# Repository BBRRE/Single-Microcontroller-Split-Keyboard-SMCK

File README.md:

# Single-Microcontroller-Split-Keyboard-SMCK
Design for a split keyboard that only uses a singular microcontroller, passive side uses a cascade of shift registors to send data through a singular serial wire leaving the 2 sides connected by only 5 wires (GND, VCC, CLK, PL, DATA)

## Schematics

## Front of the PCB

## Back of the PCB

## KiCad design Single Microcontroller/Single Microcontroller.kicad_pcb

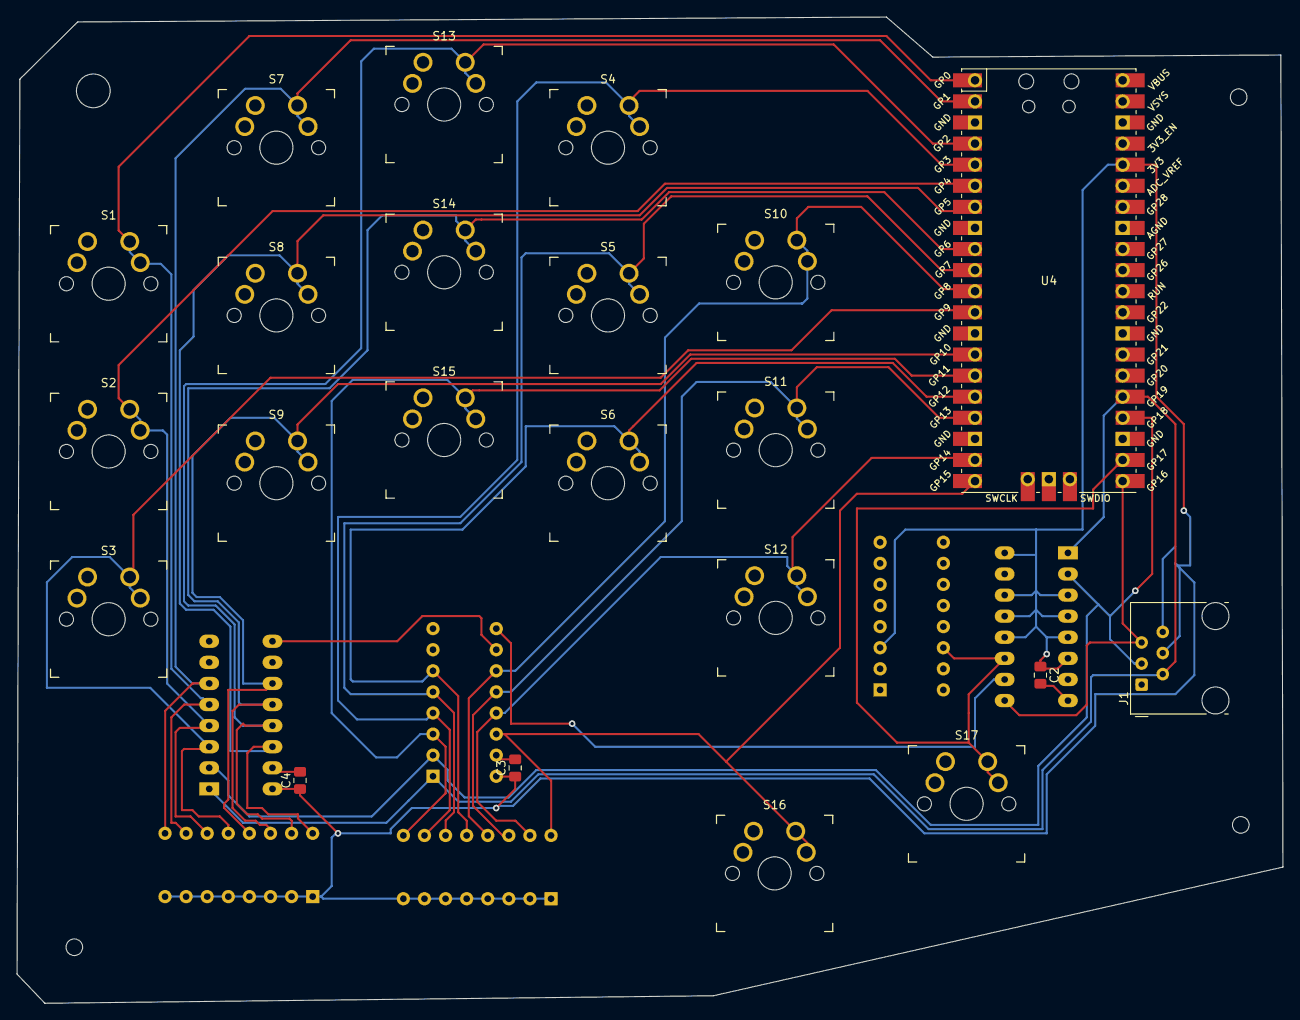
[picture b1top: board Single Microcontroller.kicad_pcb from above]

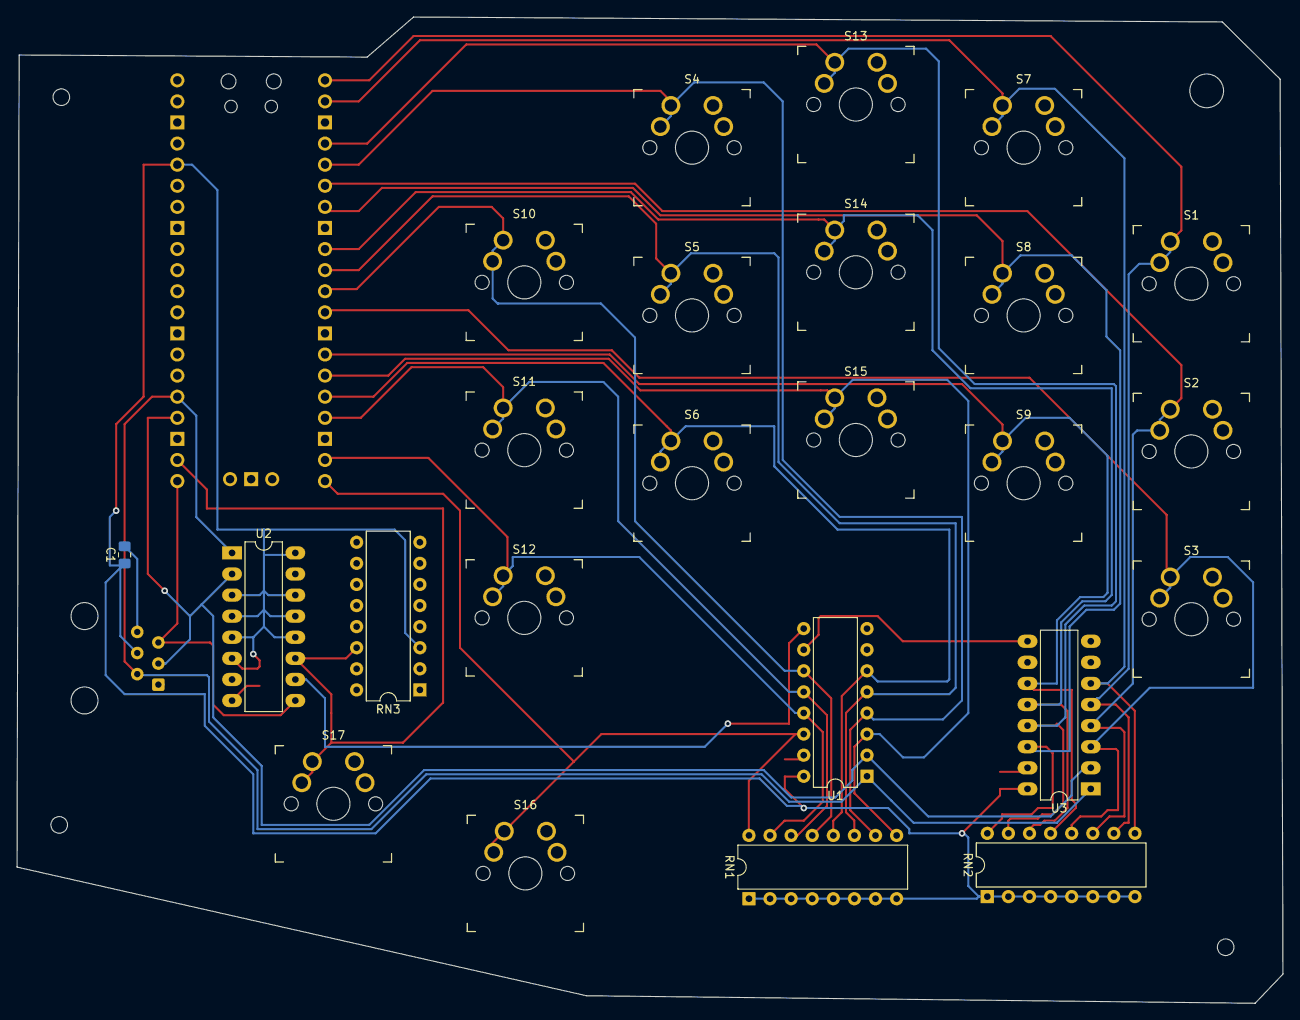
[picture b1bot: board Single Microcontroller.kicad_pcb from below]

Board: 2 copper layers, 152.4 x 118.8 mm, 29 parts (7 on the bottom side), 24 nets.

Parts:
C1, C2, C3, C4: C; C_0805_2012Metric_Pad1.18x1.45mm_HandSolder
J1: RJ12; RJ12_Amphenol_54601-x06_Horizontal
RN1, RN2, RN3: R_Pack08; DIP-16_W7.62mm
S1, S2, S3, S4, S5, S6, S7, S8, S9, S10, S11, S12, S13, S14, S15, S16, S17: Keyswitch; SW_MX_reversible
U1: 74HC165; DIP-16_W7.62mm
U2, U3: 74HC165; DIP-16_W7.62mm_LongPads
U4: Pico; RPi_Pico_SMD_TH

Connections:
3.3V: C1.1, C2.1, C3.1, C4.1, J1.4, RN1.1 (R1.1), RN1.2 (R2.1), RN1.3 (R3.1), RN1.4 (R4.1), RN1.5 (R5.1), RN1.6 (R6.1), RN1.7 (R7.1), RN1.8 (R8.1), RN2.1 (R1.1), RN2.2 (R2.1), RN2.3 (R3.1), RN2.4 (R4.1), RN2.5 (R5.1), RN2.6 (R6.1), RN2.7 (R7.1), RN2.8 (R8.1), RN3.3 (R3.1), U1.16 (VCC), U2.3 (D4), U2.4 (D5), U2.5 (D6), U2.6 (D7), U2.12 (D1), U2.13 (D2), U2.14 (D3), U2.16 (VCC), U3.16 (VCC), U4.36 (3V3)
CLK: J1.3, U1.2 (CP), U2.2 (CP), U3.2 (CP), U4.24 (GPIO18)
DATA: J1.5, U2.9 (Q7), U4.21 (GPIO16)
GND: C1.2, C2.2, C3.2, C4.2, J1.1, J1.6, S1.1, S2.1, S3.1, S4.1, S5.1, S6.1, S7.1, S8.1, S9.1, S10.1, S11.1, S12.1, S13.1, S14.1, S15.1, S16.1, S17.1, U1.8 (GND), U1.15 (~CE), U2.8 (GND), U2.15 (~CE), U3.8 (GND), U3.10 (DS), U3.15 (~CE), U4.3 (GND), U4.8 (GND), U4.13 (GND), U4.18 (GND), U4.23 (GND), U4.28 (GND), U4.38 (GND)
LinkA: U1.10 (DS), U3.9 (Q7)
LinkB: U1.9 (Q7), U2.10 (DS)
PL: J1.2, U1.1 (~PL), U2.1 (~PL), U3.1 (~PL), U4.25 (GPIO19)
S1: RN2.10 (R7.2), S1.2, U3.5 (D6), U4.1 (GPIO0)
S2: RN2.11 (R6.2), S2.2, U3.4 (D5), U4.6 (GPIO4)
S3: RN2.12 (R5.2), S3.2, U3.3 (D4), U4.12 (GPIO9)
S4: RN1.10 (R7.2), S4.2, U1.4 (D5), U4.5 (GPIO3)
S5: RN1.11 (R6.2), S5.2, U1.5 (D6), U4.10 (GPIO7)
S6: RN1.12 (R5.2), S6.2, U1.6 (D7), U4.16 (GPIO12)
S7: RN2.9 (R8.2), S7.2, U3.6 (D7), U4.2 (GPIO1)
S8: RN2.16 (R1.2), S8.2, U3.14 (D3), U4.7 (GPIO5)
S9: RN2.13 (R4.2), S9.2, U3.11 (D0), U4.14 (GPIO10)
S10: RN1.13 (R4.2), S10.2, U1.11 (D0), U4.11 (GPIO8)
S11: RN1.14 (R3.2), S11.2, U1.12 (D1), U4.17 (GPIO13)
S12: RN1.15 (R2.2), S12.2, U1.13 (D2), U4.19 (GPIO14)
S13: RN2.15 (R2.2), S13.2, U3.13 (D2), U4.4 (GPIO2)
S14: RN2.14 (R3.2), S14.2, U3.12 (D1), U4.9 (GPIO6)
S15: RN1.9 (R8.2), S15.2, U1.3 (D4), U4.15 (GPIO11)
S16: RN1.16 (R1.2), S16.2, U1.14 (D3), U4.20 (GPIO15)
S17: RN3.14 (R3.2), S17.2, U2.11 (D0), U4.22 (GPIO17)
